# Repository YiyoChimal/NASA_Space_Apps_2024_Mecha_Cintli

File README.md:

# NASA_Space_Apps_2024_Mecha_Cintli
## Problem
Leveraging Earth Observation Data for Informed Agricultural Decision-Making

## About
The project was addressed with a Sensor module (Shield Root) and a transmitter-emitter module (Shield Root Collector) along with real-time weather data and other data processed by the API, will provide the user with alerts, recommendations, and access to sensor information through a mobile app (Crop Shield).

## Information
According to the previous information the In this repository you will find:

### Document  
Explain how we addressed the project

### Video
Gives an explanation of the project

https://www.youtube.com/watch?v=-H7Pz4I1s2s

### Physical prototypes of the IOT solution 
Include the Electonic and PCB desing, the code of the micro controlers that were use, and the CAD desing of prototipes ( Sensor module (Shield Root) and a transmitter-emitter module (Shield Root Collector)). 

#### Sensor module (Shield Root)

#### Transmitter-emitter module (Shield Root Collector)

### Mobile app (Crop Shield) .
It includes the code of the app and an explanation of how it works. 

## APK
It is also included in the Mobile app folder but we wanted to give the direct link to download it at the begining of the repository. It is only for Android Users.  
[https://drive.google.com/drive/folders/1fvuNX0HjZaQjQwP62DIENjsXHxgcTP6A?usp=drive_link]

### API
The code of the Api and an explanation of how it works.

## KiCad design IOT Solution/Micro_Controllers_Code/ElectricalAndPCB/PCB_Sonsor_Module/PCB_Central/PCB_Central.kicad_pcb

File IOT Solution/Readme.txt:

# IOT Solution

## Information of the file
In this file you can find the C code of the microcontrollers use at the prototypes, the electrical and pcb design that was mede using KiCad and the Cad design that can give you the over view of how can be the product .

## General Description:
We design two prototypes to obtain real time information about the conditions of the crop and send it to a server via internet, where all the information can be analise to give the user by his app advises or the harsh data. All this is achive by using varios mudules of sensor that have to be located all over the crop field that send the infomation to a main unit. All the information is transmited using a LoRa Protocol that have a wide range of data tranmision. 

## Sensor Module
General specifications:
Devise that obtain information about the conditions of the crop like thanks to it sensor. The variables that can meassure are: Soil moisture, atmospheric humidity, atmospheric temperature, atmospheric pressure, PH and nutrients. And send the information to the Resiver-Tranmiter Module using a LoRa protocol every 1h but it can be configure on the Resiver-Tranmiter Module.

## Resiver-Tranmiter Module
General specifications:
This module it is used to configure the sesnoses modules, it sends the indication for them to send the information using the LoRa Comunication, and it sends the data obtained from all the sensors to a server via the Internet where it is processed for analysis.
It is connected to internet via an Ethernet port

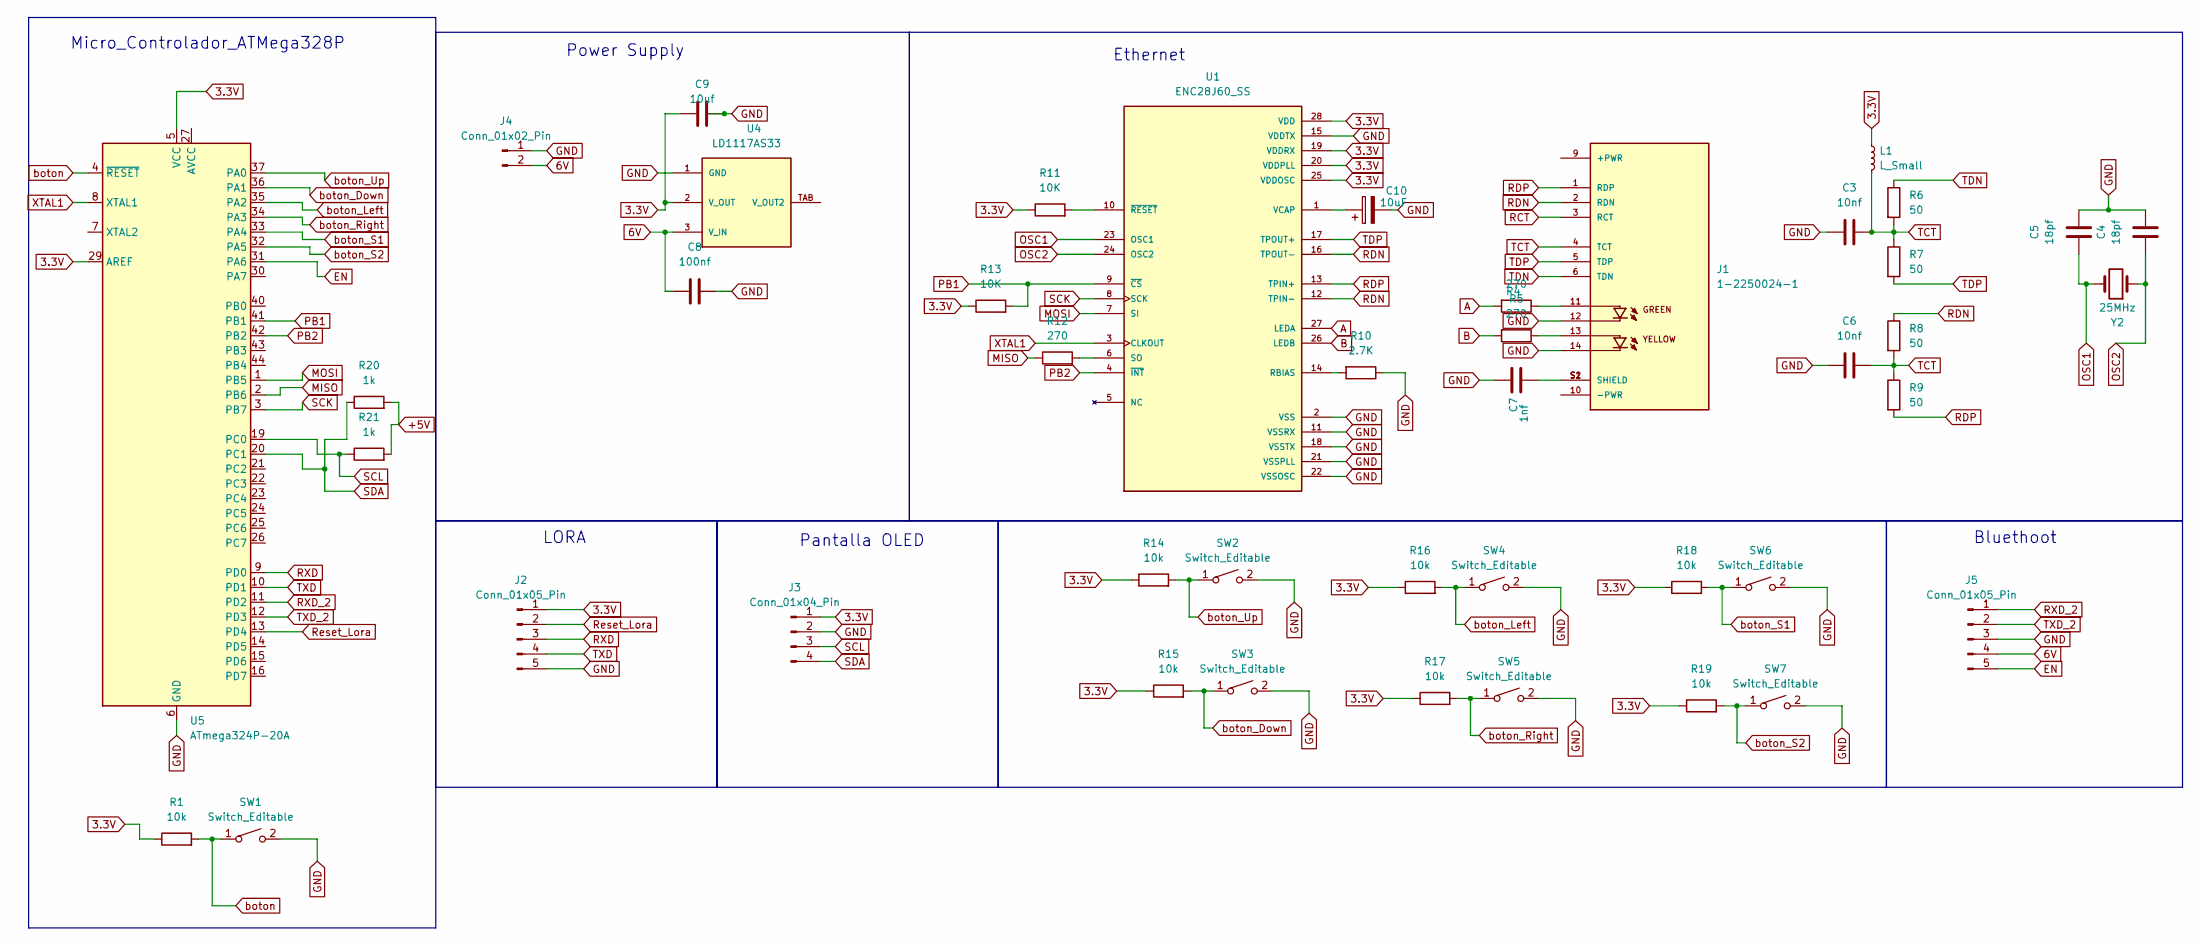
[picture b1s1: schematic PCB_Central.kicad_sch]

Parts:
C3, C6: 10nf; C_Disc_D5.0mm_W2.5mm_P5.00mm
C4, C5: 18pf; C_Disc_D5.0mm_W2.5mm_P5.00mm
C7: 1nf; C_Disc_D5.0mm_W2.5mm_P5.00mm
C8: 100nf; C_Disc_D5.0mm_W2.5mm_P5.00mm
C9: 10uf; C_Disc_D5.0mm_W2.5mm_P5.00mm
C10: 10uF; CP_Radial_D4.0mm_P1.50mm
J1: 1-2250024-1; BEL_1-2250024-1; PARTREV E
J2, J5: Conn_01x05_Pin; PinHeader_1x05_P2.54mm_Vertical
J3: Conn_01x04_Pin; JST_XH_B4B-XH-AM_1x04_P2.50mm_Vertical
J4: Conn_01x02_Pin; BarrelJack_CLIFF_FC681465S_SMT_Horizontal
L1: L_Small; L_1812_4532Metric_Pad1.30x3.40mm_HandSolder
R1, R14, R15, R16, R17, R18, R19: 10k; R_1206_3216Metric
R4, R5, R12: 270; R_1206_3216Metric
R6, R7, R8, R9: 50; R_1206_3216Metric
R10: 2.7K; R_1206_3216Metric
R11, R13: 10K; R_1206_3216Metric
R20, R21: 1k; R_1206_3216Metric
SW1, SW2, SW3, SW4, SW5, SW6, SW7: Switch_Editable; SW_PUSH_6mm_H7.3mm
U1: ENC28J60_SS; SOP65P780X200-28N; PARTREV E
U4: LD1117AS33; SOT223
U5: ATmega324P-20A; TQFP-44_10x10mm_P0.8mm
Y2: 25MHz; Crystal_HC49-4H_Vertical

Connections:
3.3V: C9.1, J2.1, J3.1, L1.1, R1.1, R11.1, R13.1, R14.1, R15.1, R16.1, R17.1, R18.1, R19.1, U1.19 (VDDRX), U1.20 (VDDPLL), U1.25 (VDDOSC), U1.28 (VDD), U4.2 (V_OUT), U5.5 (VCC), U5.17 (VCC), U5.29 (AREF), U5.38 (VCC)
6V: C8.1, J4.2, J5.4, U4.3 (V_IN)
+5V: R20.2, R21.2
A: R4.2, U1.27 (LEDA)
B: R5.2, U1.26 (LEDB)
EN: J5.5, U5.31 (PA6)
GND: C3.1, C4.2, C5.2, C6.1, C7.1, C8.2, C9.2, C10.2, J1.12, J1.14, J2.5, J3.2, J4.1, J5.3, R10.1, SW1.2, SW2.2, SW3.2, SW4.2, SW5.2, SW6.2, SW7.2, U1.2 (VSS), U1.11 (VSSRX), U1.15 (VDDTX), U1.18 (VSSTX), U1.21 (VSSPLL), U1.22 (VSSOSC), U4.1 (GND), U5.6 (GND), U5.18 (GND), U5.28 (GND), U5.39 (GND)
MISO: R12.1, U5.2 (PB6)
MOSI: U1.7 (SI), U5.1 (PB5)
unnamed: C7.2, J1.S1 (SHIELD), J1.S2 (SHIELD)
unnamed: J1.11, R4.1
unnamed: J1.13, R5.1
unnamed: R10.2, U1.14 (RBIAS)
unnamed: R12.2, U1.6 (SO)
unnamed: C10.1, U1.1 (VCAP)
unnamed: R11.2, U1.10 (~RESET)
OSC1: C5.1, U1.23 (OSC1), Y2.2
OSC2: C4.1, U1.24 (OSC2), Y2.1
PB1: R13.2, U1.9 (~CS), U5.41 (PB1)
PB2: U1.4 (~INT), U5.42 (PB2)
RCT: J1.3 (RCT)
RDN: J1.2 (RDN), R8.1, U1.12 (TPIN-), U1.16 (TPOUT-)
RDP: J1.1 (RDP), R9.2, U1.13 (TPIN+)
RXD: J2.3, U5.9 (PD0)
RXD_2: J5.1, U5.11 (PD2)
Reset_Lora: J2.2, U5.13 (PD4)
SCK: U1.8 (SCK), U5.3 (PB7)
SCL: J3.3, R21.1, U5.19 (PC0)
SDA: J3.4, R20.1, U5.20 (PC1)
TCT: C3.2, C6.2, J1.4 (TCT), L1.2, R6.2, R7.1, R8.2, R9.1
TDN: J1.6 (TDN), R6.1
TDP: J1.5 (TDP), R7.2, U1.17 (TPOUT+)
TXD: J2.4, U5.10 (PD1)
TXD_2: J5.2, U5.12 (PD3)
XTAL1: U1.3 (CLKOUT), U5.8 (XTAL1)
boton: R1.2, SW1.1, U5.4 (~RESET)
boton_Down: R15.2, SW3.1, U5.36 (PA1)
boton_Left: R16.2, SW4.1, U5.35 (PA2)
boton_Right: R17.2, SW5.1, U5.34 (PA3)
boton_S1: R18.2, SW6.1, U5.33 (PA4)
boton_S2: R19.2, SW7.1, U5.32 (PA5)
boton_Up: R14.2, SW2.1, U5.37 (PA0)

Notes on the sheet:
Power Supply
Micro_Controlador_ATMega328P
Bluethoot
LORA
Ethernet
Pantalla OLED

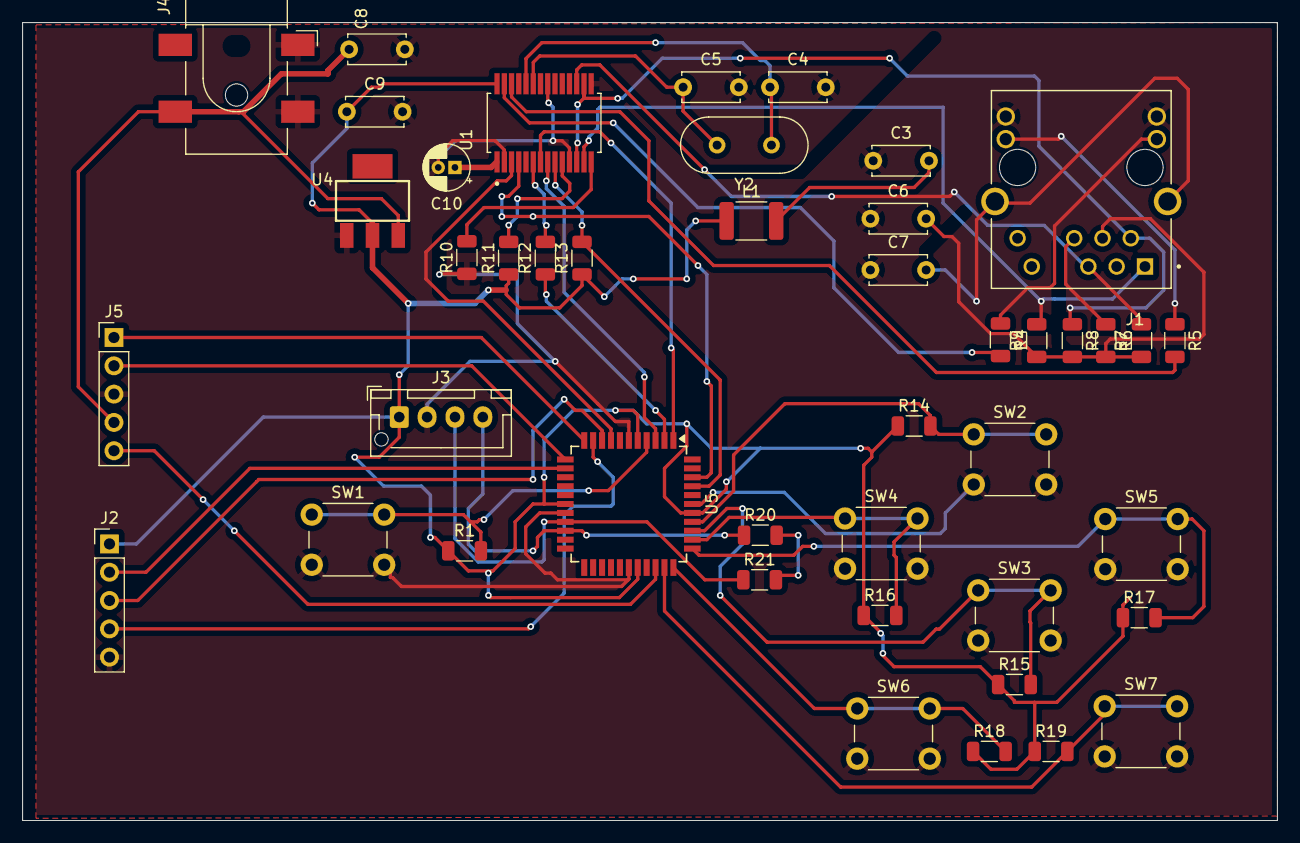
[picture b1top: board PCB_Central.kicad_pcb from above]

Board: 2 copper layers, 112.6 x 71.6 mm, 44 parts (0 on the bottom side), 41 nets.

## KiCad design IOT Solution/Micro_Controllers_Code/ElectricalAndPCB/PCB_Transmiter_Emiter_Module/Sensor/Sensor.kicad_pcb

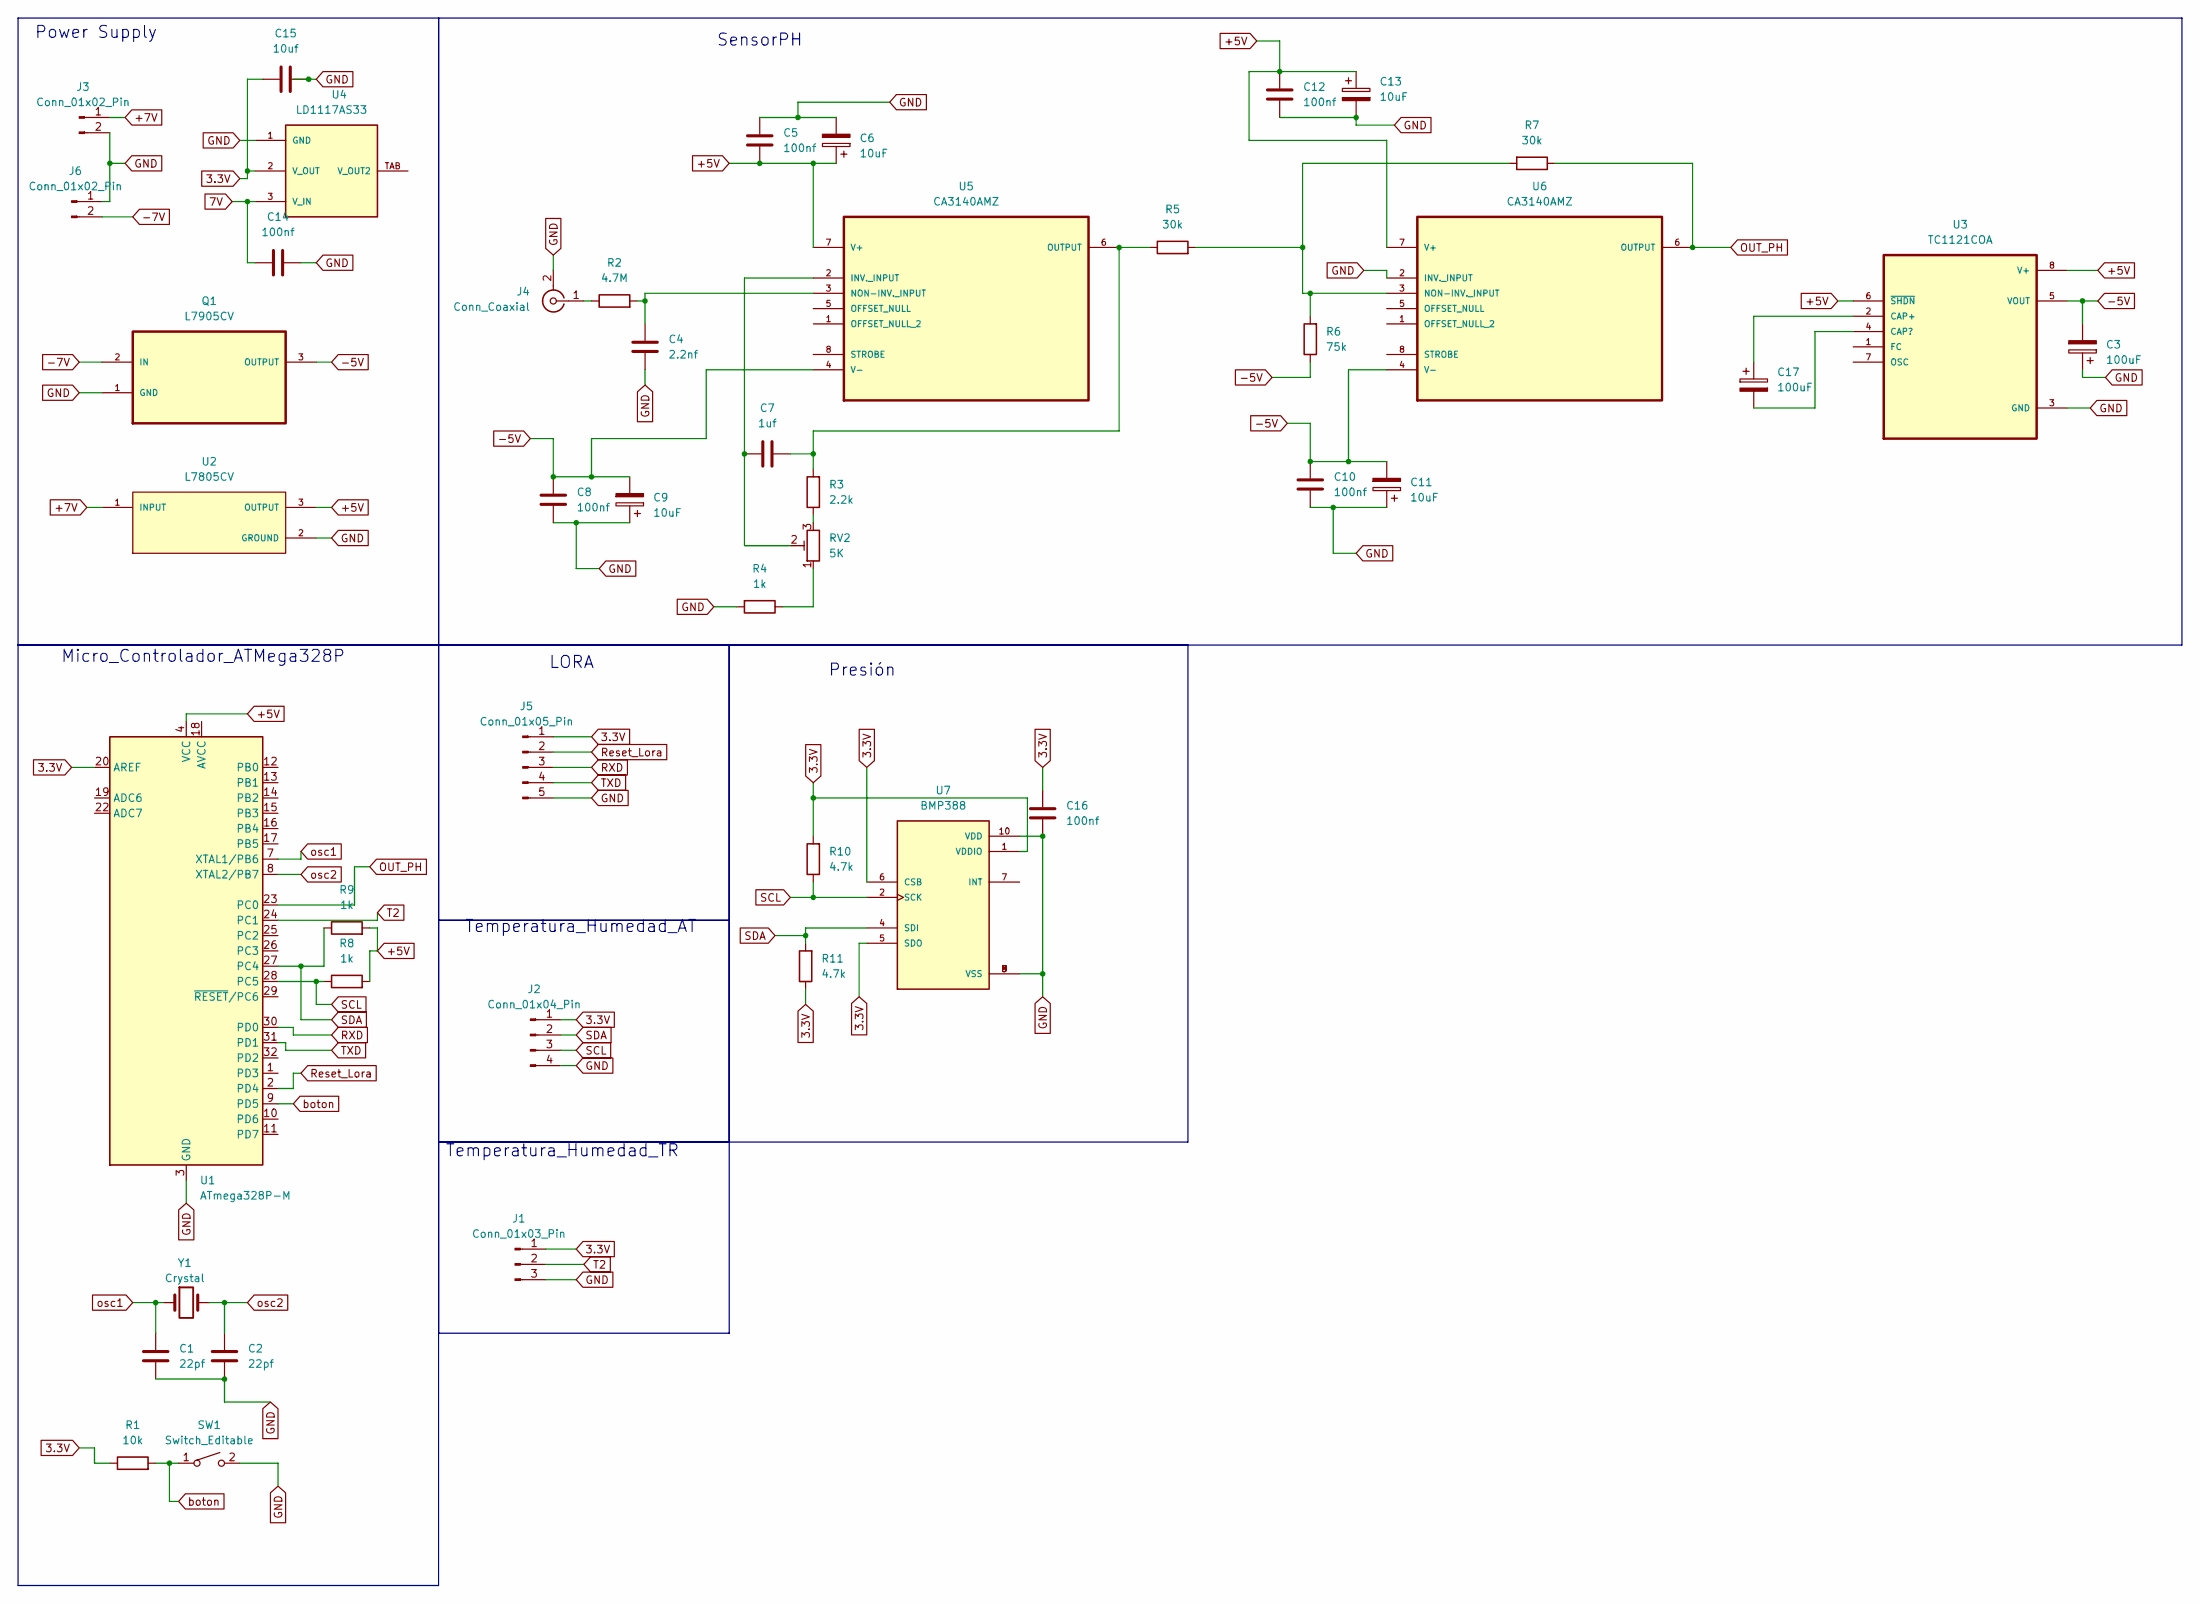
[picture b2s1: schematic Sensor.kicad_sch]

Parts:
C1, C2: 22pf; C_Disc_D5.0mm_W2.5mm_P5.00mm
C3, C17: 100uF; CP_Radial_D4.0mm_P1.50mm
C4: 2.2nf; C_Disc_D5.0mm_W2.5mm_P5.00mm
C5, C8, C10, C12, C14, C16: 100nf; C_Disc_D5.0mm_W2.5mm_P5.00mm
C6, C9, C11, C13: 10uF; CP_Radial_D4.0mm_P1.50mm
C7: 1uf; C_Disc_D5.0mm_W2.5mm_P5.00mm
C15: 10uf; C_Disc_D5.0mm_W2.5mm_P5.00mm
J1: Conn_01x03_Pin; JST_XA_B03B-XASK-1_1x03_P2.50mm_Vertical
J2: Conn_01x04_Pin; JST_XH_B4B-XH-AM_1x04_P2.50mm_Vertical
J3, J6: Conn_01x02_Pin; JST_XH_B2B-XH-AM_1x02_P2.50mm_Vertical
J4: Conn_Coaxial; BNC_Amphenol_B6252HB-NPP3G-50_Horizontal
J5: Conn_01x05_Pin; PinHeader_1x05_P2.54mm_Vertical
Q1: L7905CV; TO254P450X1020X1935-3P; MPN L7905CV
R1: 10k; R_1206_3216Metric
R2: 4.7M; R_1206_3216Metric
R3: 2.2k; R_1206_3216Metric
R4, R8, R9: 1k; R_1206_3216Metric
R5, R7: 30k; R_1206_3216Metric
R6: 75k; R_1206_3216Metric
R10, R11: 4.7k; R_1206_3216Metric
RV2: 5K; Potentiometer_Bourns_3296W_Vertical
SW1: Switch_Editable; SW_PUSH_6mm_H7.3mm
U1: ATmega328P-M; TQFP-32_7x7mm_P0.8mm
U2: L7805CV; TO255P1040X460X1968-3; PARTREV 36
U3: TC1121COA; SOIC127P599X175-8N
U4: LD1117AS33; SOT223
U5, U6: CA3140AMZ; SOIC127P600X175-8N; MPN CA3140AMZ
U7: BMP388; PQFN50P200X200X80-10N; PARTREV 1.1
Y1: Crystal; Crystal_HC49-4H_Vertical

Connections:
3.3V: C15.1, C16.2, J1.1, J2.1, J5.1, R1.1, R10.2, R11.1, U1.20 (AREF), U4.2 (V_OUT), U7.1 (VDDIO), U7.5 (SDO), U7.6 (CSB)
7V: C14.1, U4.3 (V_IN)
+5V: C5.2, C6.1, C12.1, C13.1, R8.2, R9.2, U1.4 (VCC), U1.6 (VCC), U2.3 (OUTPUT), U3.6 (~SHDN), U3.8 (V+), U5.7 (V+), U6.7 (V+)
+7V: J3.1, U2.1 (INPUT)
-5V: C3.2, C8.1, C9.2, C10.1, C11.2, Q1.3 (OUTPUT), R6.1, U3.5 (VOUT), U5.4 (V-), U6.4 (V-)
-7V: J6.2, Q1.2 (IN)
GND: C1.2, C2.2, C3.1, C4.2, C5.1, C6.2, C8.2, C9.1, C10.2, C11.1, C12.2, C13.2, C14.2, C15.2, C16.1, J1.3, J2.4, J3.2, J4.2 (Ext), J5.5, J6.1, Q1.1 (GND), R4.2, SW1.2, U1.3 (GND), U1.5 (GND), U1.21 (GND), U1.33 (GND), U2.2 (GROUND), U3.3 (GND), U4.1 (GND), U6.2 (INV._INPUT), U7.3 (VSS), U7.8 (VSS), U7.9 (VSS), U7.10 (VDD)
unnamed: J4.1 (In), R2.1
unnamed: R3.1, RV2.3
unnamed: R4.1, RV2.1
unnamed: C17.1, U3.2 (CAP+)
unnamed: C17.2, U3.4 (CAP?)
unnamed: C7.1, RV2.2, U5.2 (INV._INPUT)
unnamed: C4.1, R2.2, U5.3 (NON-INV._INPUT)
unnamed: C7.2, R3.2, R5.1, U5.6 (OUTPUT)
unnamed: R5.2, R6.2, R7.2, U6.3 (NON-INV._INPUT)
OUT_PH: R7.1, U1.23 (PC0), U6.6 (OUTPUT)
RXD: J5.3, U1.30 (PD0)
Reset_Lora: J5.2, U1.2 (PD4)
SCL: J2.3, R8.1, R10.1, U1.28 (PC5), U7.2 (SCK)
SDA: J2.2, R9.1, R11.2, U1.27 (PC4), U7.4 (SDI)
T2: J1.2, U1.24 (PC1)
TXD: J5.4, U1.31 (PD1)
boton: R1.2, SW1.1, U1.9 (PD5)
osc1: C1.1, U1.7 (XTAL1/PB6), Y1.1
osc2: C2.1, U1.8 (XTAL2/PB7), Y1.2

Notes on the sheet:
Temperatura_Humedad_AT
LORA
Micro_Controlador_ATMega328P
Temperatura_Humedad_TR
SensorPH
Power Supply
Presión

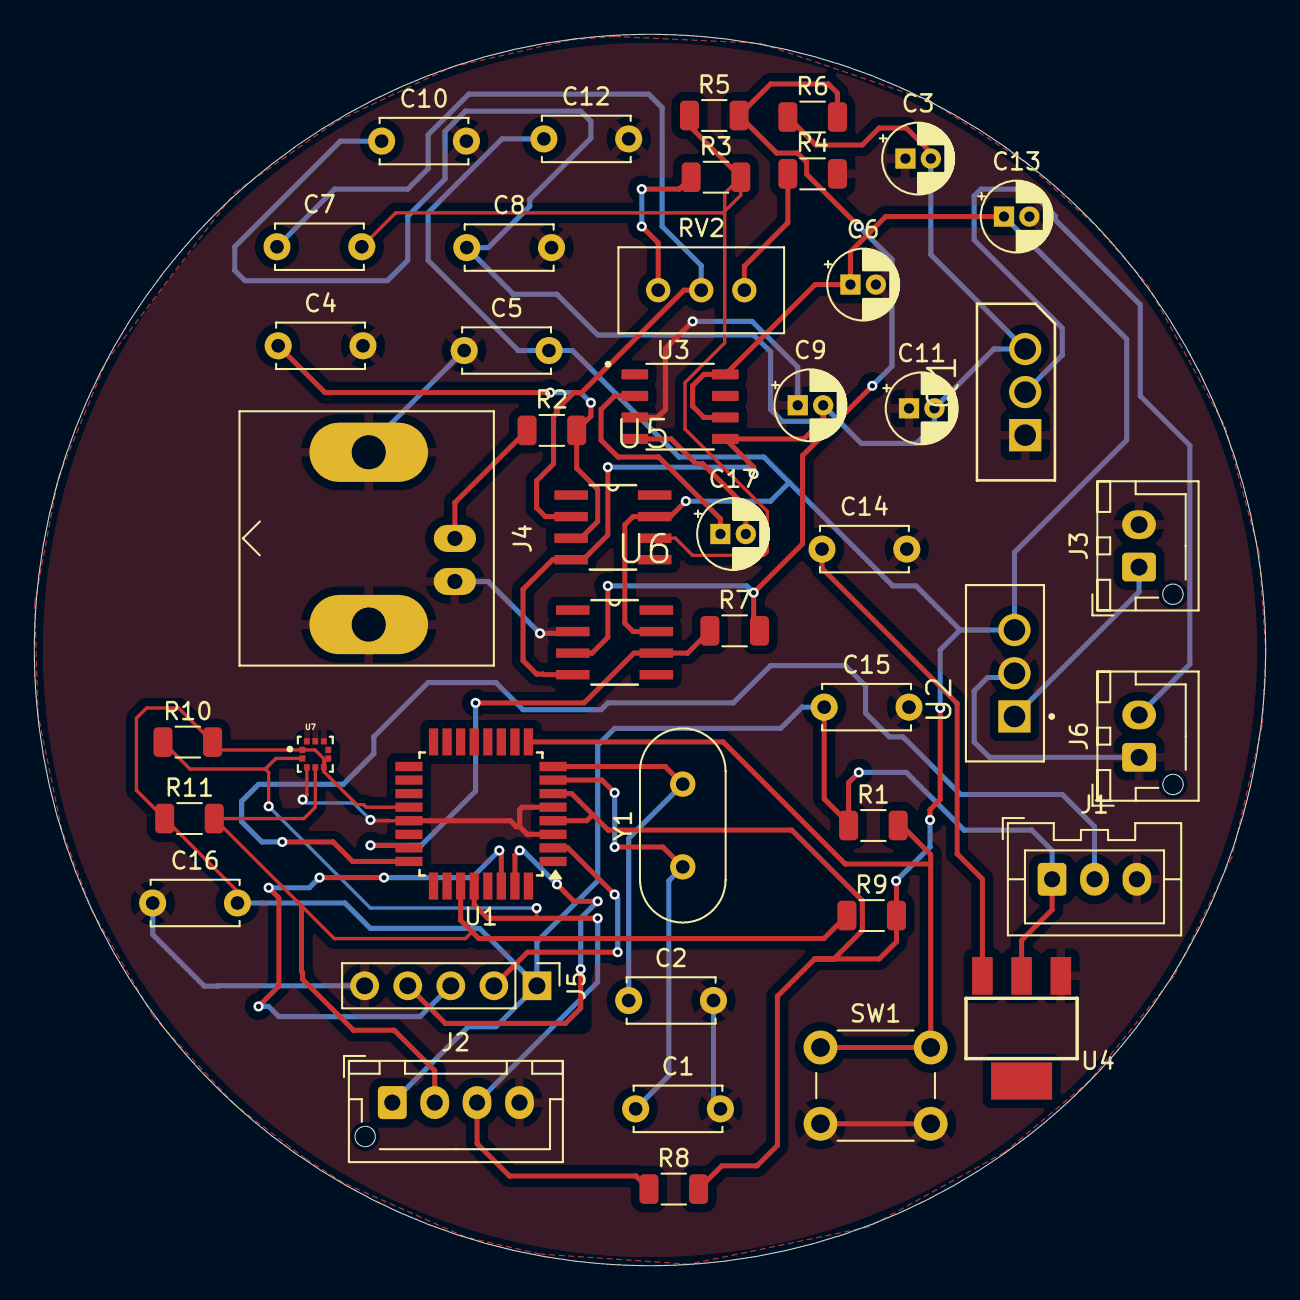
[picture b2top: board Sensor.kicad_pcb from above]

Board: 2 copper layers, 72.6 x 72.6 mm, 45 parts (0 on the bottom side), 26 nets.

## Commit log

2024-10-06 firt commit this commit contains the sing up page and initial structure
2024-10-06 finish front auth screens
2024-10-06 home page nearly finished
2024-10-06 add navbar styles
2024-10-06 add forum page
2024-10-06 finish home pages
2024-10-06 Add locator
2024-10-06 update readme file
2024-10-06 fix readme Styles
2024-10-06 readme test?
2024-10-06 test
2024-10-06 Initialize firebase
2024-10-06 API
    funciones principales para la api que procesa la informacion climatologica
2024-10-06 initialized firabase 2
2024-10-06 Complete API Implemetation
    Yes
2024-10-06 Delete openWeatherKey.txt
    No longer needed now on /API/
2024-10-06 Delete main.py
    No longer needed now on /API/
2024-10-06 Delete idealConditionsForCrops.csv
    No longer needed now on /API/
2024-10-06 parte2
2024-10-07 revert
2024-10-07 Version 0.0.1
2024-10-07 main.py
2024-10-07 AppMbile
2024-10-07 Create APK_App_Link
2024-10-07 Update APK_App_Link
